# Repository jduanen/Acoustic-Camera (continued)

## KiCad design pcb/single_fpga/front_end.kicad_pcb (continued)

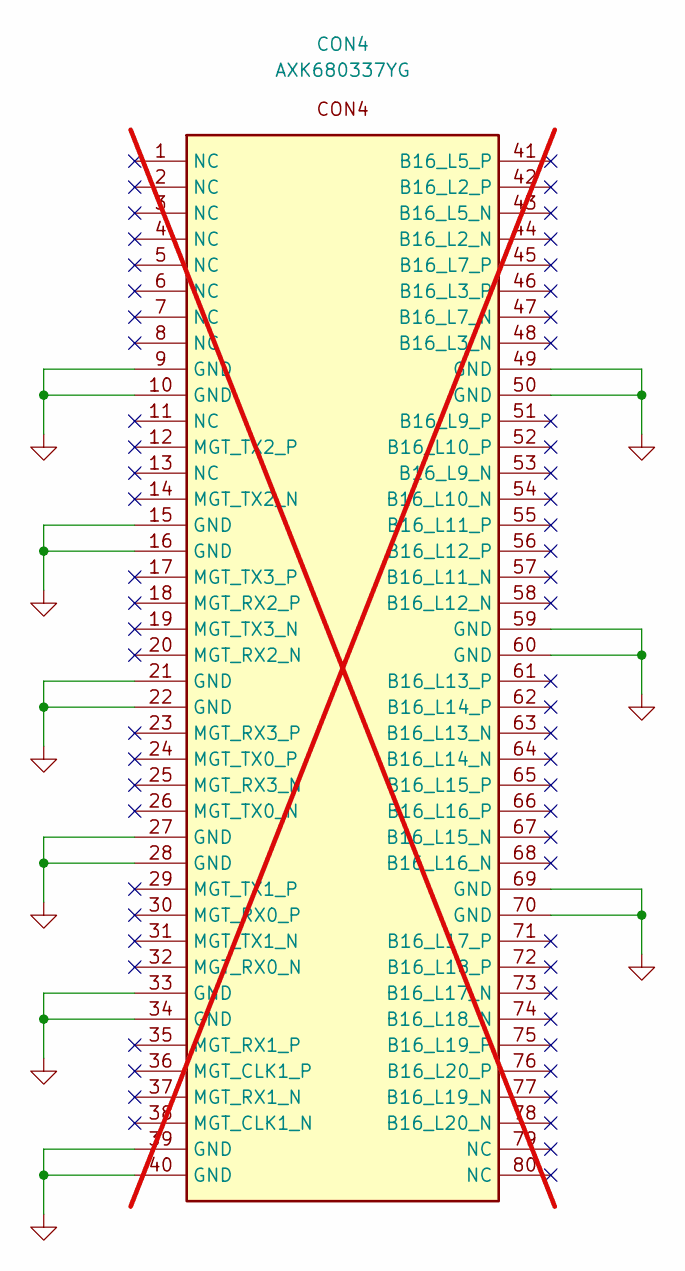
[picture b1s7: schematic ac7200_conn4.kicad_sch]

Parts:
CON4: AXK680337YG; Part Number AXK680337YG; LCSC Part # C2848859; not fitted

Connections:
GND: CON4.9 (GND), CON4.10 (GND), CON4.15 (GND), CON4.16 (GND), CON4.21 (GND), CON4.22 (GND), CON4.27 (GND), CON4.28 (GND), CON4.33 (GND), CON4.34 (GND), CON4.39 (GND), CON4.40 (GND), CON4.49 (GND), CON4.50 (GND), CON4.59 (GND), CON4.60 (GND), CON4.69 (GND), CON4.70 (GND); also elsewhere on the board

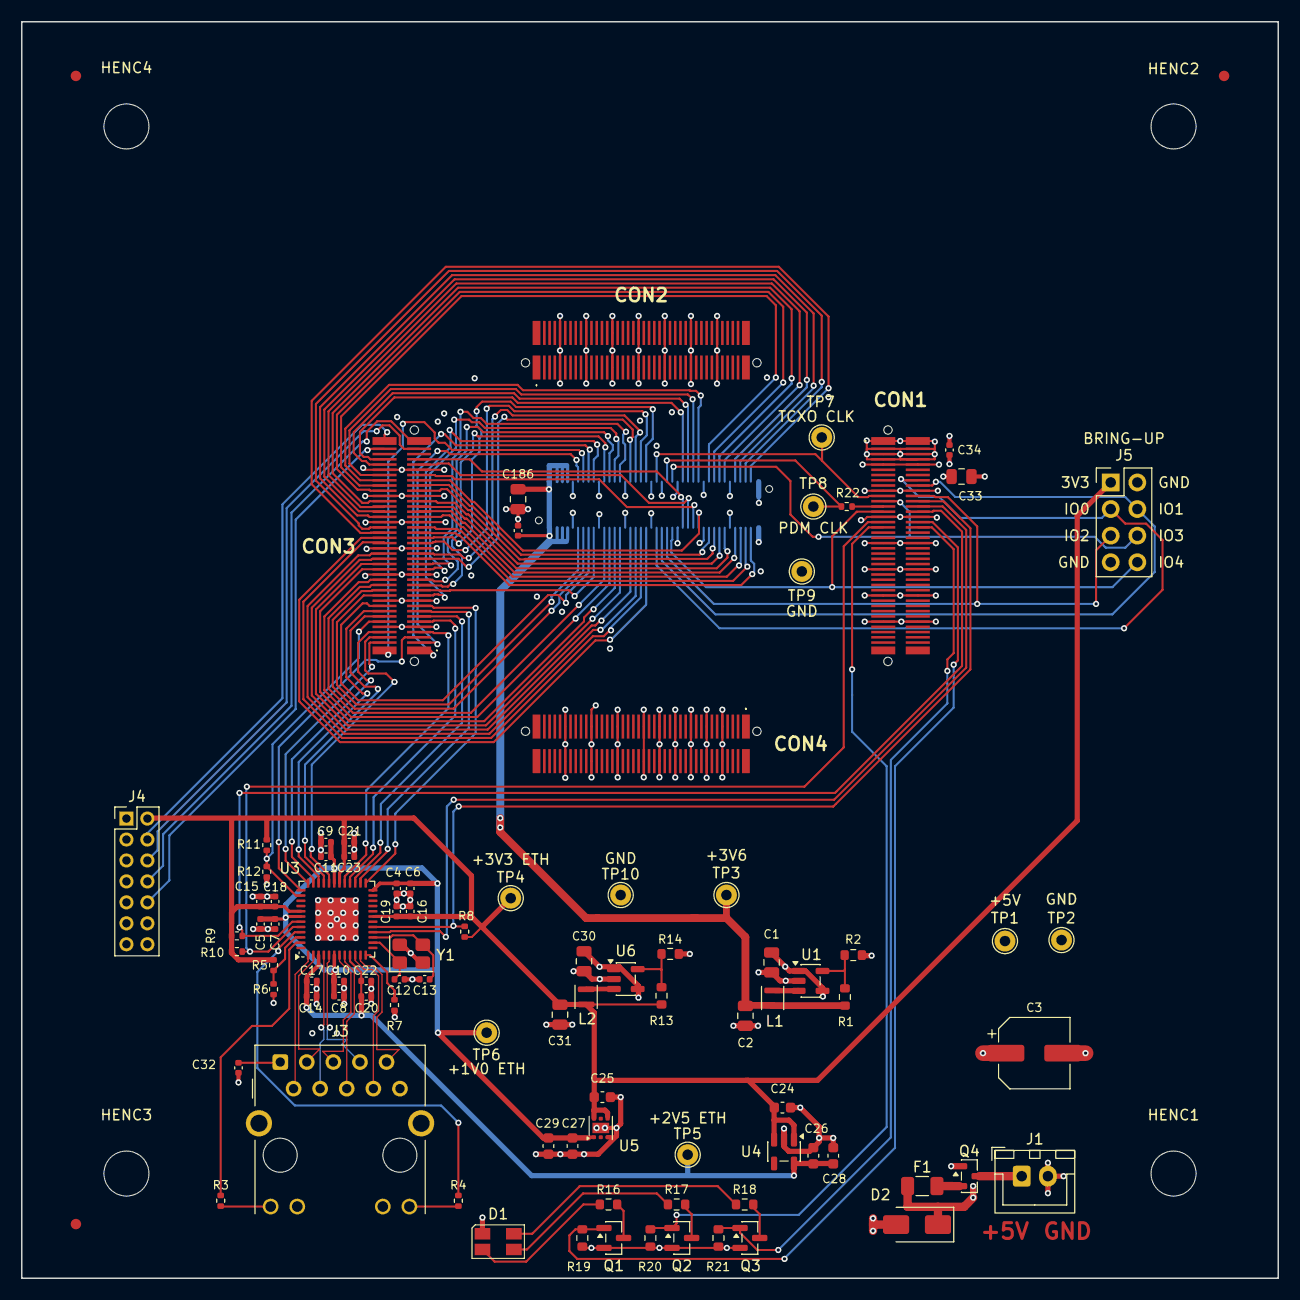
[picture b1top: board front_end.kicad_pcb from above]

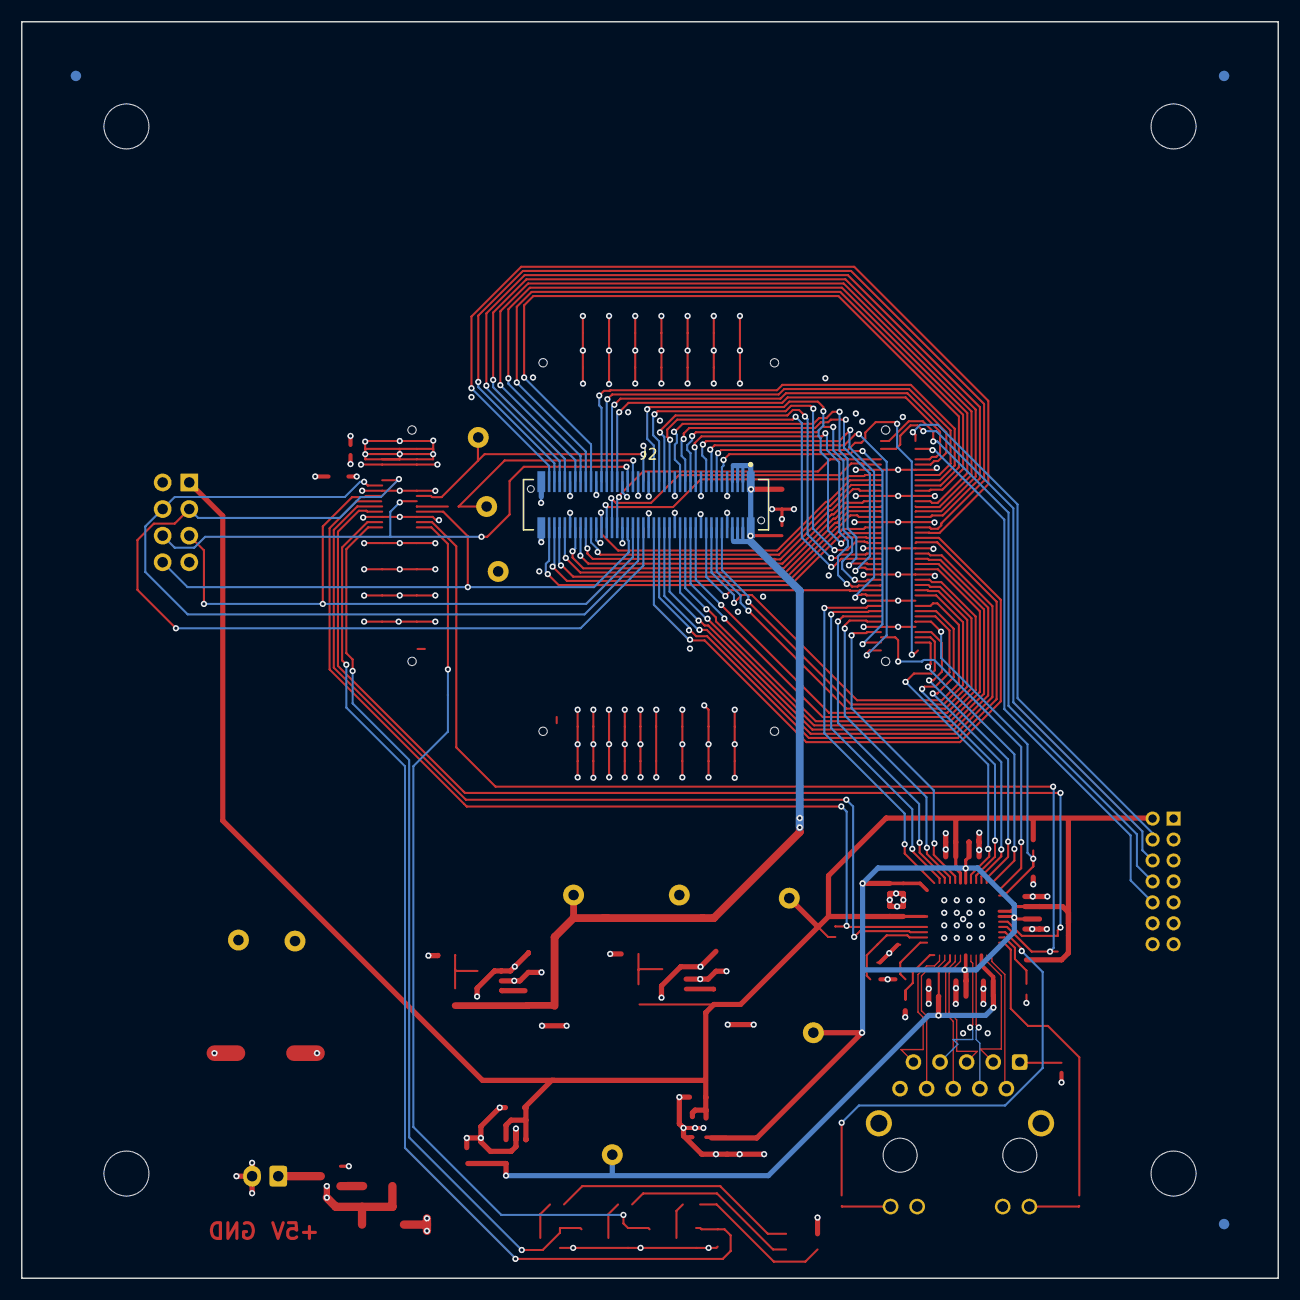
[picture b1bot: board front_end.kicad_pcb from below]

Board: 4 copper layers, 120.0 x 120.0 mm, 101 parts (4 on the bottom side), 114 nets.

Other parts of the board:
FID1, FID2, FID3, FID4, FID5, FID6: Fiducial_1mm_Mask2mm
HENC1, HENC2, HENC3, HENC4: MountingHole_4.3mm_M4

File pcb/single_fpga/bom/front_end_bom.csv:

"Refs","Qty","Value","Footprint","Manufacturer","Part Number","LCSC Part #","PROD_ID","Tolerance","Voltage","Description"
"C1,C30","2","4.7uF","Capacitor_SMD:C_0805_2012Metric","Samsung Electro-Mechanics","CL21B475KOFNNNE","C107365","","10%","16V","Unpolarized capacitor"
"C2,C31,C186","3","10uF","Capacitor_SMD:C_0805_2012Metric","Murata","GRM21BR71A106KE51L","C86038","","10%","10V","Unpolarized capacitor"
"C3","1","100uF","Capacitor_SMD:CP_Elec_6.3x5.8","FOSAN","FVM025ADA101M0654","C7469933","CAP-12547","20%","25V","Polarized capacitor, US symbol, 0.248"" Dia x 0.303"" H, Electrolitic"
"C4,C5,C8,C9,C14,C15,C16,C20,C21","9","1uF","Capacitor_SMD:C_0402_1005Metric","Samsung Electro-Mechanics","CL05A105KA5NQNC","C52923","","","",""
"C6,C7,C10,C11,C17,C18,C19,C22,C23,C32,C34,C187","12","0.1uF","Capacitor_SMD:C_0402_1005Metric","Samsung Electro-Mechanics","CL05B104KO5NNNC","C1525","","10%","16V","Unpolarized capacitor"
"C12,C13","2","15pF","Capacitor_SMD:C_0402_1005Metric","FH (Guangdong Fenghua)","0402CG150J500NT","C1548","","","",""
"C24,C25,C26,C27","4","10uF","Capacitor_SMD:C_0603_1608Metric","Samsung Electro-Mechanics","CL10A106KP8NNNC","C19702","","","",""
"C28,C29","2","10nF","Capacitor_SMD:C_0603_1608Metric","FH (Guangdong Fenghua)","0603B103K500NT","C57112","","","",""
"C33","1","22uF","Capacitor_SMD:C_0805_2012Metric","Samsung Electro-Mechanics","CL21A226MAQNNNE","C45783","","","",""
"CON1,CON3","2","AXK680337YG","AXK680337YG:AXK680337YG","Panasonic","AXK680337YG","C2848859","","","","Carrier-side CON1 for the ALINX AC7200 SOM: Panasonic AXK680337YG P5K 80-pin 0.5mm header (3.0mm mated, bosses), mating the module's AXK580137YG socket CON1. Pin names are the AC7200 signals on module CON1 (from unit A of 'AC7200 Interface', same pin positions); pin numbers 1-80 are the header's, socket pin n mates header pin n.,Carrier-side CON3 for the ALINX AC7200 SOM: Panasonic AXK680337YG P5K 80-pin 0.5mm header (3.0mm mated, bosses), mating the module's AXK580137YG socket CON3. Pin names are the AC7200 signals on module CON3 (from unit C of 'AC7200 Interface', same pin positions); pin numbers 1-80 are the header's, socket pin n mates header pin n."
"D1","1","ASMB-MTB0-0A3A2","LED_SMD:LED_Avago_PLCC4_3.2x2.8mm_CW","Broadcom","ASMB-MTB0-0A3A2","C2686824","","","","Tricolor Black Surface LED, Common Anode Pin 1, PLCC-4"
"D2","1","SMAJ5.0A","Diode_SMD:D_SMA","Littelfuse","SMAJ5.0A","C83329","","","","400W unidirectional Transient Voltage Suppressor, 5.0Vr, SMA(DO-214AC)"
"F1","1","1.5A","Fuse:Fuse_1206_3216Metric","BHFUSE","BSMD1206-150-16V","C883133","","","","Resettable fuse, polymeric positive temperature coefficient"
"J1","1","Main Power Input","Connector_JST:JST_XH_B2B-XH-A_1x02_P2.50mm_Vertical","JST","B2B-XH-A(LF)(SN)","C158012","","","","Generic connector, single row, 01x02, script generated (kicad-library-utils/schlib/autogen/connector/)"
"J2","1","AXK5S80337YG","AXK5S80337YG:AXK5S80337YG","Panasonic","AXK5S80337YG","C5572475","","","","Panasonic AXK5S80337YG -- P5KS 0.5mm-pitch 80-pin board-to-board SOCKET, 7.0/8.0/9.0mm mated height, with positioning bosses. Mates AXK6S80637YG at 9.0mm."
"J3","1","HR911130A","HR911130A:HR911130A","HanRun","HR911130A","C54408","","","","Single-port 10/100/1000Base-T RJ45 jack with integrated magnetics + Bob-Smith termination + Green/Yellow LEDs"
"J4","1","JTAG_HDR_2x7_2mm","Connector_PinHeader_2.00mm:PinHeader_2x07_P2.00mm_Vertical","HCTL","PZ200-2-07-Z","C2905993","","","","Xilinx Platform Cable USB JTAG target header (DS593 pinout)"
"J5","1","Bring-up","Connector_PinHeader_2.54mm:PinHeader_2x04_P2.54mm_Vertical","hanxia","HX PZ2.54-2x4P ZZ","C32713277","","","","Bring-up header: +3V3_ETH, GND, AUX_IO0-4 (FPGA bank 13, LVCMOS33; also on J2 pins 42/44/46/47/48)"
"L1,L2","2","2.2uH","Inductor_SMD:L_Murata_DFE201610P","Murata","DFE201612E-2R2M=P2","C337893","","","","2.2uH, Isat>2.4A, Imax>=1.8A, Rdc<=120mOhms, shielded"
"Q1,Q2,Q3","3","2N7002","Package_TO_SOT_SMD:SOT-23","JSCJ","2N7002","C8545","","","","0.115A Id, 60V Vds, N-Channel MOSFET, SOT-23"
"Q4","1","AO3401A","Package_TO_SOT_SMD:SOT-23","AOS","AO3401A","C15127","","","","Reverse-polarity protection for the +5V input (gate to GND: conducts only with correct polarity)"
"R1","1","549k","Resistor_SMD:R_0603_1608Metric","YAGEO","RC0603FR-07549KL","C245978","","1%","","Resistor"
"R2","1","100k","Resistor_SMD:R_0603_1608Metric","UNI-ROYAL","0603WAF1003T5E","C25803","","1%","","Resistor"
"R3,R4","2","330","PCM_SparkFun-Resistor:R_0402_1005Metric","UNI-ROYAL","0402WGF3300TCE","C25104","RES-15407","","","Resistor"
"R7","1","11k 1%","PCM_SparkFun-Resistor:R_0402_1005Metric","UNI-ROYAL","0402WGF1102TCE","C25749","RES-25567","","","Resistor"
"R8,R10","2","2.2k","SparkFun-Resistor:R_0402_1005Metric","UNI-ROYAL","0402WGF2201TCE","C25879","RES-08272","","","Resistor"
"R9","1","10k","SparkFun-Resistor:R_0402_1005Metric","UNI-ROYAL","0402WGF1002TCE","C25744","RES-00824","","","Resistor"
"R11","1","5.76k 1%","PCM_SparkFun-Resistor:R_0402_1005Metric","UNI-ROYAL","0402WGF5761TCE","C25910","RES-25566","","","Resistor"
"R12","1","2.49k 1%","PCM_SparkFun-Resistor:R_0402_1005Metric","UNI-ROYAL","0402WGF2491TCE","C25884","RES-25566","","","Resistor"
"R13","1","453k 1%","Resistor_SMD:R_0603_1608Metric","Panasonic","ERJ-3EKF4533V","C403234","","1%","","Resistor"
"R14","1","100k 1%","Resistor_SMD:R_0603_1608Metric","UNI-ROYAL","0603WAF1003T5E","C25803","","1%","","Resistor"
"R16","1","620","PCM_SparkFun-Resistor:R_0603_1608Metric","UNI-ROYAL","0603WAF6200T5E","C23220","RES-07856","","","Resistor"
"R17,R18","2","390","PCM_SparkFun-Resistor:R_0603_1608Metric","UNI-ROYAL","0603WAF3900T5E","C23151","RES-07856","","","Resistor"
"R19,R20,R21","3","100k","PCM_SparkFun-Resistor:R_0603_1608Metric","UNI-ROYAL","0603WAF1003T5E","C25803","RES-07856","","","Resistor"
"R22","1","33","PCM_SparkFun-Resistor:R_0402_1005Metric","UNI-ROYAL","0402WGF330JTCE","C25105","RES-15407","","","Resistor"
"U1,U6","2","TLV62569DBV","Package_TO_SOT_SMD:SOT-23-5","Texas Instruments","TLV62569DBVR","C141836","","","","High Efficiency Synchronous Buck Converter, Adjustable Output 0.6V-5.5V, 2A, SOT-23-5"
"U3","1","DP83867IRRGZ","Package_DFN_QFN:VQFN-48-1EP_7x7mm_P0.5mm_EP4.1x4.1mm","Texas Instruments","DP83867IRRGZR","C2678038","","","",""
"U4","1","TLV74325PDBV","Package_TO_SOT_SMD:SOT-23-5","Texas Instruments","TLV74325PDBVR","C485154","","","","500mA Low Dropout Voltage Regulator, Fixed Output 2.5V, SOT-23-5"
"U5","1","TLV75710PDRV","Package_SON:WSON-6-1EP_2x2mm_P0.65mm_EP1x1.6mm","Texas Instruments","TLV75710PDRVR","C2861391","","","","500mA Low Dropout Voltage Regulator, Fixed Output 1.0V, WSON6"
"Y1","1","25MHz ±50 ppm max parallel resonant","Crystal:Crystal_SMD_3225-4Pin_3.2x2.5mm","YXC","X322525MOB4SI","C9006","","","","Four pin crystal, GND on pins 2 and 4"

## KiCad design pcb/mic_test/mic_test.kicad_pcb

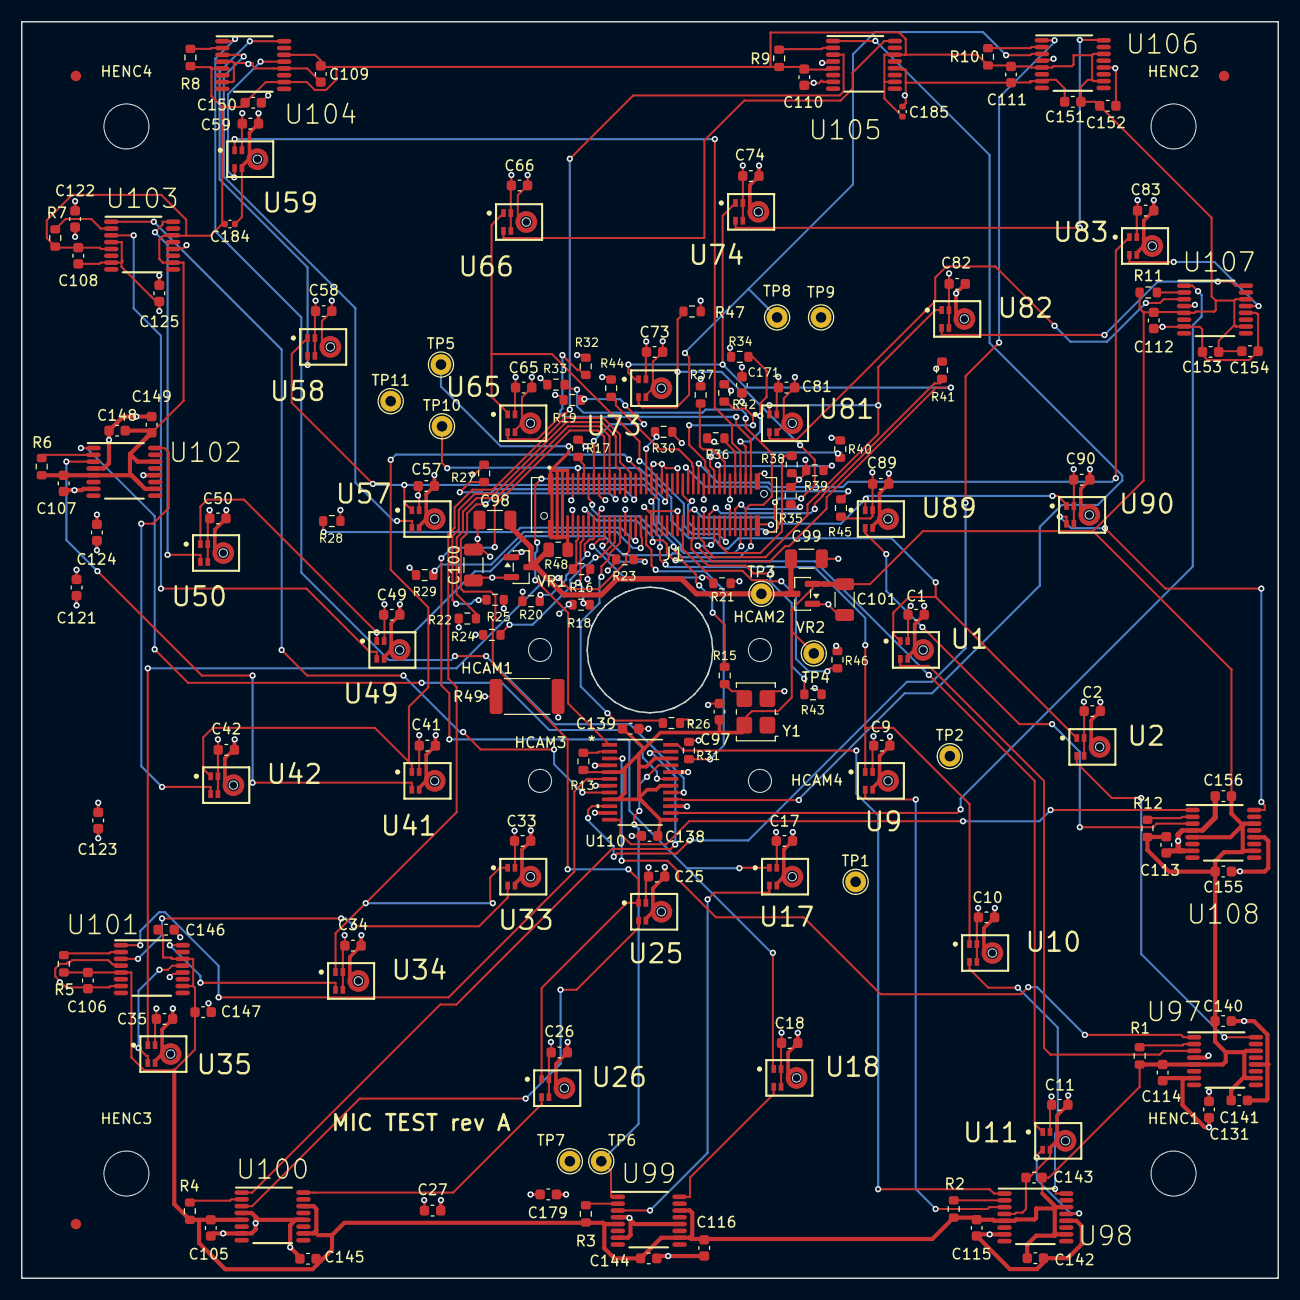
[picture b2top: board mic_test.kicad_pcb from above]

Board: 4 copper layers, 120.0 x 120.0 mm, 190 parts (0 on the bottom side), 109 nets.

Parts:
C1, C2, C9, C10, C11, C17, C18, C25, C26, C27, C33, C34, C35, C41, C42, C49, C50, C57, C58, C59, C65, C66, C73, C74, C81, C82, C83, C89, C90, C97, C105, C106, C107, C108, C109, C110, C111, C112, C113, C114, C115, C116, C121, C122, C123, C124, C125, C131, C138, C139, C140, C141, C142, C143, C144, C145, C146, C147, C148, C149, C150, C151, C152, C153, C154, C155, C156, C171, C179: 100nF; C_0603_1608Metric
C98, C99, C100, C101: 1uF; C_1206_3216Metric
C184, C185: 100nF; C_0402_1005Metric
FID1, FID2, FID3: Fiducial_1mm_Mask2mm
HCAM1, HCAM2, HCAM3, HCAM4: MountingHole_2.2mm_M2
HENC1, HENC2, HENC3, HENC4: MountingHole_4.3mm_M4
J1: AXK6S80637YG
R1, R2, R3, R4, R5, R6, R7, R8, R9, R10, R11, R12, R13, R16, R17, R18, R19, R20, R21, R22, R23, R24, R25, R26, R27, R28, R29, R30, R31, R32, R33, R34, R35, R36, R37, R38, R39, R40, R41, R42, R43, R44, R45, R46, R47: 10k; R_0603_1608Metric
R15: 33; R_0603_1608Metric
R48: 0.1 1%; R_0805_2012Metric
R49: 51 DNP; R_2512_6332Metric
TP1, TP7, TP9, TP11: GND; TestPoint_THTPad_D2.0mm_Drill1.0mm
TP2: MIC 3V3; TestPoint_THTPad_D2.0mm_Drill1.0mm
TP3: 3V6; TestPoint_THTPad_D2.0mm_Drill1.0mm
TP4: CLK 3V3; TestPoint_THTPad_D2.0mm_Drill1.0mm
TP5: 3V6 IN; TestPoint_THTPad_D2.0mm_Drill1.0mm
TP6: ARM02 CLK; TestPoint_THTPad_D2.0mm_Drill1.0mm
TP8: MIC72 CLK; TestPoint_THTPad_D2.0mm_Drill1.0mm
TP10: DATA00; TestPoint_THTPad_D2.0mm_Drill1.0mm
U1, U2, U9, U10, U11, U17, U18, U25, U26, U33, U34, U35, U41, U42, U49, U50, U57, U58, U59, U65, U66, U73, U74, U81, U82, U83, U89, U90: IM72D128V01XTMA1; IFX-PG-LLGA-5-4
U97, U98, U99, U100, U101, U102, U103, U104, U105, U106, U107, U108: LMK1C1108PW; PW0016A_N
U110: CDCLVC1112PW; PW24
VR1, VR2: MCP1700T-3302E/TT; SOT-23
Y1: ASFL1-12.288MHZ; Oscillator_SMD_SeikoEpson_SG8002LB-4Pin_5.0x3.2mm

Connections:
+3V6: J1.1, J1.2, J1.3, J1.4, J1.5, J1.6, J1.7, J1.8, R48.1, TP5.1 (1_1)
+3V6_A: C98.1, C99.1, R48.2, TP3.1 (1_1), VR1.3 (VI), VR2.3 (VI)
ARM_00_CLK: U97.1 (CLKIN), U110.3 (Y0)
ARM_01_CLK: U98.1 (CLKIN), U110.24 (Y1)
ARM_02_CLK: TP6.1 (1_1), U99.1 (CLKIN), U110.21 (Y2)
ARM_03_CLK: U100.1 (CLKIN), U110.23 (Y3)
ARM_04_CLK: U101.1 (CLKIN), U110.6 (Y4)
ARM_05_CLK: U102.1 (CLKIN), U110.19 (Y5)
ARM_06_CLK: U103.1 (CLKIN), U110.8 (Y6)
ARM_07_CLK: U104.1 (CLKIN), U110.17 (Y7)
ARM_08_CLK: U105.1 (CLKIN), U110.16 (Y8)
ARM_09_CLK: U106.1 (CLKIN), U110.10 (Y9)
ARM_10_CLK: U107.1 (CLKIN), U110.14 (Y10)
ARM_11_CLK: U108.1 (CLKIN), U110.12 (Y11)
CLK_3V3: C97.1, C101.1, C105.2, C106.1, C107.2, C108.2, C109.2, C110.2, C111.2, C112.2, C113.2, C114.2, C115.1, C116.2, C138.1, C139.1, C140.1, C141.1, C142.1, C143.1, C144.1, C145.1, C146.1, C147.1, C148.1, C149.1, C150.1, C151.1, C152.1, C153.1, C154.1, C155.1, C156.1, C184.1, C185.1, R1.2, R2.2, R3.2, R4.2, R5.2, R6.2, R7.2, R8.2, R9.2, R10.2, R11.2, R12.2, R13.2, TP4.1 (1_1), U97.5 (VDD), U97.10 (VDD), U97.14 (VDD), U98.5 (VDD), U98.10 (VDD), U98.14 (VDD), U99.5 (VDD), U99.10 (VDD), U99.14 (VDD), U100.5 (VDD), U100.10 (VDD), U100.14 (VDD), U101.5 (VDD), U101.10 (VDD), U101.14 (VDD), U102.5 (VDD), U102.10 (VDD), U102.14 (VDD), U103.5 (VDD), U103.10 (VDD), U103.14 (VDD), U104.5 (VDD), U104.10 (VDD), U104.14 (VDD), U105.5 (VDD), U105.10 (VDD), U105.14 (VDD), U106.5 (VDD), U106.10 (VDD), U106.14 (VDD), U107.5 (VDD), U107.10 (VDD), U107.14 (VDD), U108.5 (VDD), U108.10 (VDD), U108.14 (VDD), U110.5 (VDD), U110.9 (VDD), U110.13 (VDD), U110.18 (VDD), U110.22 (VDD), VR2.2 (VO), Y1.4
DATA_00: J1.11, TP10.1 (1_1), U1.1 (DATA), U2.1 (DATA)
DATA_01: J1.12, R16.1
DATA_02: J1.13, R17.1
DATA_03: J1.14, R18.1
DATA_04: J1.15, U9.1 (DATA), U10.1 (DATA)
DATA_05: J1.16, U11.1 (DATA)
DATA_06: J1.17, R19.1
DATA_07: J1.18, R20.1
DATA_08: J1.21, U17.1 (DATA), U18.1 (DATA)
DATA_09: J1.22, R21.1
DATA_10: J1.23, R22.1
DATA_11: J1.24, R23.1
DATA_12: J1.25, U25.1 (DATA), U26.1 (DATA)
DATA_13: J1.26, R24.1
DATA_14: J1.27, R25.1
DATA_15: J1.28, R26.1
DATA_16: J1.31, U33.1 (DATA), U34.1 (DATA)
DATA_17: J1.32, U35.1 (DATA)
DATA_18: J1.33, R27.1
DATA_19: J1.34, R28.1
DATA_20: J1.35, U41.1 (DATA), U42.1 (DATA)
DATA_21: J1.36, R29.1
DATA_22: J1.37, R30.1
DATA_23: J1.38, R31.1
DATA_24: J1.78, U49.1 (DATA), U50.1 (DATA)
DATA_25: J1.77, R32.1
DATA_26: J1.76, R33.1
DATA_27: J1.75, R34.1
DATA_28: J1.74, U57.1 (DATA), U58.1 (DATA)
DATA_29: J1.73, U59.1 (DATA)
DATA_30: J1.72, R35.1
DATA_31: J1.71, R36.1
DATA_32: J1.68, U65.1 (DATA), U66.1 (DATA)
DATA_33: J1.67, R37.1
DATA_34: J1.66, R38.1
DATA_35: J1.65, R39.1
DATA_36: J1.64, U73.1 (DATA), U74.1 (DATA)
DATA_37: J1.63, R40.1
DATA_38: J1.62, R41.1
DATA_39: J1.61, R42.1
DATA_40: J1.58, U81.1 (DATA), U82.1 (DATA)
DATA_41: J1.57, U83.1 (DATA)
DATA_42: J1.56, R43.1
DATA_43: J1.55, R44.1
DATA_44: J1.54, U89.1 (DATA), U90.1 (DATA)
DATA_45: J1.53, R45.1
DATA_46: J1.52, R46.1
DATA_47: J1.51, R47.1
GND: C1.2, C2.2, C9.2, C10.2, C11.2, C17.2, C18.2, C25.2, C26.2, C27.2, C33.2, C34.2, C35.2, C41.2, C42.2, C49.2, C50.2, C57.2, C58.2, C59.2, C65.2, C66.2, C73.2, C74.2, C81.2, C82.2, C83.2, C89.2, C90.2, C97.2, C98.2, C99.2, C100.2, C101.2, C105.1, C106.2, C107.1, C108.1, C109.1, C110.1, C111.1, C112.1, C113.1, C114.1, C115.2, C116.1, C121.2, C122.2, C123.2, C124.2, C125.2, C131.2, C138.2, C139.2, C140.2, C141.2, C142.2, C143.2, C144.2, C145.2, C146.2, C147.2, C148.2, C149.2, C150.2, C151.2, C152.2, C153.2, C154.2, C155.2, C156.2, C171.2, C179.2, C184.2, C185.2, J1.9, J1.10, J1.19, J1.20, J1.29, J1.30, J1.39, J1.40, J1.43, J1.49, J1.50, J1.59, J1.60, J1.69, J1.70, J1.79, J1.80, R49.2, TP1.1 (1_1), TP7.1 (1_1), TP9.1 (1_1), TP11.1 (1_1), U1.4 (SEL), U1.5 (GND), U2.5 (GND), U9.4 (SEL), U9.5 (GND), U10.5 (GND), U11.4 (SEL), U11.5 (GND), U17.4 (SEL), U17.5 (GND), U18.5 (GND), U25.4 (SEL), U25.5 (GND), U26.5 (GND), U33.4 (SEL), U33.5 (GND), U34.5 (GND), U35.4 (SEL), U35.5 (GND), U41.4 (SEL), U41.5 (GND), U42.5 (GND), U49.4 (SEL), U49.5 (GND), U50.5 (GND), U57.4 (SEL), U57.5 (GND), U58.5 (GND), U59.4 (SEL), U59.5 (GND), U65.4 (SEL), U65.5 (GND), U66.5 (GND), U73.4 (SEL), U73.5 (GND), U74.5 (GND), U81.4 (SEL), U81.5 (GND), U82.5 (GND), U83.4 (SEL), U83.5 (GND), U89.4 (SEL), U89.5 (GND), U90.5 (GND), U97.4 (GND), U97.7 (GND), U97.12 (GND), U98.4 (GND), U98.7 (GND), U98.12 (GND), U99.4 (GND), U99.7 (GND), U99.12 (GND), U100.4 (GND), U100.7 (GND), U100.12 (GND), U101.4 (GND), U101.7 (GND), U101.12 (GND), U102.4 (GND), U102.7 (GND), U102.12 (GND), U103.4 (GND), U103.7 (GND), U103.12 (GND), U104.4 (GND), U104.7 (GND), U104.12 (GND), U105.4 (GND), U105.7 (GND), U105.12 (GND), U106.4 (GND), U106.7 (GND), U106.12 (GND), U107.4 (GND), U107.7 (GND), U107.12 (GND), U108.4 (GND), U108.7 (GND), U108.12 (GND), U110.4 (GND), U110.7 (GND), U110.11 (GND), U110.15 (GND), U110.20 (GND), VR1.1 (GND), VR2.1 (GND), Y1.2
MIC_3V3: C1.1, C2.1, C9.1, C10.1, C11.1, C17.1, C18.1, C25.1, C26.1, C27.1, C33.1, C34.1, C35.1, C41.1, C42.1, C49.1, C50.1, C57.1, C58.1, C59.1, C65.1, C66.1, C73.1, C74.1, C81.1, C82.1, C83.1, C89.1, C90.1, C100.1, C121.1, C122.1, C123.1, C124.1, C125.1, C131.1, C171.1, C179.1, R16.2, R17.2, R18.2, R19.2, R20.2, R21.2, R22.2, R23.2, R24.2, R25.2, R26.2, R27.2, R28.2, R29.2, R30.2, R31.2, R32.2, R33.2, R34.2, R35.2, R36.2, R37.2, R38.2, R39.2, R40.2, R41.2, R42.2, R43.2, R44.2, R45.2, R46.2, R47.2, R49.1, TP2.1 (1_1), U1.2 (VDD), U2.2 (VDD), U2.4 (SEL), U9.2 (VDD), U10.2 (VDD), U10.4 (SEL), U11.2 (VDD), U17.2 (VDD), U18.2 (VDD), U18.4 (SEL), U25.2 (VDD), U26.2 (VDD), U26.4 (SEL), U33.2 (VDD), U34.2 (VDD), U34.4 (SEL), U35.2 (VDD), U41.2 (VDD), U42.2 (VDD), U42.4 (SEL), U49.2 (VDD), U50.2 (VDD), U50.4 (SEL), U57.2 (VDD), U58.2 (VDD), U58.4 (SEL), U59.2 (VDD), U65.2 (VDD), U66.2 (VDD), U66.4 (SEL), U73.2 (VDD), U74.2 (VDD), U74.4 (SEL), U81.2 (VDD), U82.2 (VDD), U82.4 (SEL), U83.2 (VDD), U89.2 (VDD), U90.2 (VDD), U90.4 (SEL), VR1.2 (VO)
MIC_CLK_00: U1.3 (CLK), U97.3 (Y0)
MIC_CLK_01: U2.3 (CLK), U97.16 (Y1)
MIC_CLK_08: U9.3 (CLK), U98.3 (Y0)
MIC_CLK_09: U10.3 (CLK), U98.16 (Y1)
MIC_CLK_10: U11.3 (CLK), U98.13 (Y2)
MIC_CLK_16: U17.3 (CLK), U99.3 (Y0)
MIC_CLK_17: U18.3 (CLK), U99.16 (Y1)
MIC_CLK_24: U25.3 (CLK), U100.3 (Y0)
MIC_CLK_25: U26.3 (CLK), U100.16 (Y1)
MIC_CLK_32: U33.3 (CLK), U101.3 (Y0)
MIC_CLK_33: U34.3 (CLK), U101.16 (Y1)
MIC_CLK_34: U35.3 (CLK), U101.13 (Y2)
MIC_CLK_40: U41.3 (CLK), U102.3 (Y0)
MIC_CLK_41: U42.3 (CLK), U102.16 (Y1)
MIC_CLK_48: U49.3 (CLK), U103.3 (Y0)
MIC_CLK_49: U50.3 (CLK), U103.16 (Y1)
MIC_CLK_56: U57.3 (CLK), U104.3 (Y0)
MIC_CLK_57: U58.3 (CLK), U104.16 (Y1)
MIC_CLK_58: U59.3 (CLK), U104.13 (Y2)
MIC_CLK_64: U65.3 (CLK), U105.3 (Y0)
MIC_CLK_65: U66.3 (CLK), U105.16 (Y1)
MIC_CLK_72: TP8.1 (1_1), U73.3 (CLK), U106.3 (Y0)
MIC_CLK_73: U74.3 (CLK), U106.16 (Y1)
MIC_CLK_80: U81.3 (CLK), U107.3 (Y0)
MIC_CLK_81: U82.3 (CLK), U107.16 (Y1)
MIC_CLK_82: U83.3 (CLK), U107.13 (Y2)
MIC_CLK_88: U89.3 (CLK), U108.3 (Y0)
MIC_CLK_89: U90.3 (CLK), U108.16 (Y1)
unnamed: R1.1, U97.2 (1G)
unnamed: R2.1, U98.2 (1G)
unnamed: R3.1, U99.2 (1G)
unnamed: R4.1, U100.2 (1G)
unnamed: R5.1, U101.2 (1G)
unnamed: R6.1, U102.2 (1G)
unnamed: R7.1, U103.2 (1G)
unnamed: R8.1, U104.2 (1G)
unnamed: R9.1, U105.2 (1G)
unnamed: R10.1, U106.2 (1G)
unnamed: R11.1, U107.2 (1G)
unnamed: R12.1, U108.2 (1G)
unnamed: R13.1, U110.2 (1G)
unnamed: R15.2, Y1.3
PDM_CLK: J1.45, U110.1 (CLKIN)
TCXO_CLK: J1.41, R15.1

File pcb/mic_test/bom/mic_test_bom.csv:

"Refs","Qty","Value","Footprint","Manufacturer","Part Number","LCSC Part #","PROD_ID","Tolerance","Voltage","Description"
"C1,C2,C9,C10,C11,C17,C18,C25,C26,C27,C33,C34,C35,C41,C42,C49,C50,C57,C58,C59,C65,C66,C73,C74,C81,C82,C83,C89,C90,C97,C105,C106,C107,C108,C109,C110,C111,C112,C113,C114,C115,C116,C121,C122,C123,C124,C125,C131,C138,C139,C140,C141,C142,C143,C144,C145,C146,C147,C148,C149,C150,C151,C152,C153,C154,C155,C156,C171,C179","69","100nF","Capacitor_SMD:C_0603_1608Metric","YAGEO","CC0603KRX7R9BB104","C14663","","","","Unpolarized capacitor"
"C98,C99,C100,C101","4","1uF","Capacitor_SMD:C_1206_3216Metric","Samsung Electro-Mechanics","CL31B105KBHNNNE","C1848","","","","Unpolarized capacitor"
"C184,C185","2","100nF","Capacitor_SMD:C_0402_1005Metric","Samsung Electro-Mechanics","CL05B104KO5NNNC","C1525","","","","Unpolarized capacitor"
"J1","1","AXK6S80637YG","AXK6S80637YG:AXK6S80637YG","Panasonic","AXK6S80637YG","C2936859","","","","Panasonic AXK6S80637YG -- P5KS 0.5mm-pitch 80-pin board-to-board HEADER, 6.0/6.5/9.0mm mated height, with positioning bosses. Mates AXK5S80337YG at 9.0mm."
"R1,R2,R3,R4,R5,R6,R7,R8,R9,R10,R11,R12,R13,R16,R17,R18,R19,R20,R21,R22,R23,R24,R25,R26,R27,R28,R29,R30,R31,R32,R33,R34,R35,R36,R37,R38,R39,R40,R41,R42,R43,R44,R45,R46,R47","45","10k","PCM_SparkFun-Resistor:R_0603_1608Metric","UNI-ROYAL","0603WAF1002T5E","C25804","RES-00824","","","Resistor"
"R15","1","33","PCM_SparkFun-Resistor:R_0603_1608Metric","UNI-ROYAL","0603WAF330JT5E","C23140","","","","Resistor"
"R48","1","0.1 1%","Resistor_SMD:R_0805_2012Metric","PSA (Prosperity Dielectrics)","FBF05FTPR100-00L","C382279","","","","Resistor"
"U1,U2,U9,U10,U11,U17,U18,U25,U26,U33,U34,U35,U41,U42,U49,U50,U57,U58,U59,U65,U66,U73,U74,U81,U82,U83,U89,U90","28","IM72D128V01XTMA1","IM72D128:IFX-PG-LLGA-5-4","Infineon","IM72D128V01XTMA1","C5119248","","","","Infineon IM72D128 PDM MEMS mic, 72 dB SNR, IP57"
"U97,U98,U99,U100,U101,U102,U103,U104,U105,U106,U107,U108","12","LMK1C1108PW","CDCLVC1108:PW0016A_N","Texas Instruments","LMK1C1108PWR","C2868241","","","",""
"U110","1","CDCLVC1112PW","CDCLVC1112:PW24","Texas Instruments","CDCLVC1112PWR","C2876940","","","",""
"VR1,VR2","2","MCP1700T-3302E/TT","Package_TO_SOT_SMD:SOT-23","Microchip","MCP1700T-3302E/TT","C39051","","","","250mA Low Quiscent Current LDO, 3.3V output, SOT-23"
"Y1","1","ASFL1-12.288MHZ","Oscillator:Oscillator_SMD_SeikoEpson_SG8002LB-4Pin_5.0x3.2mm","Abracon","ASFL1-12.288MHZ-LCS-T","C276419","","","","Master clock: Abracon ASFL1-12.288MHZ-LCS-T, 12.288 MHz 3.3 V HCMOS oscillator, ±50 ppm, -40 to +85 °C, 5.0x3.2 mm. Pin 1 is tri-state (open = running) and is left unconnected."
